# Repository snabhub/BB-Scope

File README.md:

# Bread Board Scope (Mini Oscilloscope + Function Generator)
- This is the repositiory of Group 36 ELEC3300 Fall 2022.

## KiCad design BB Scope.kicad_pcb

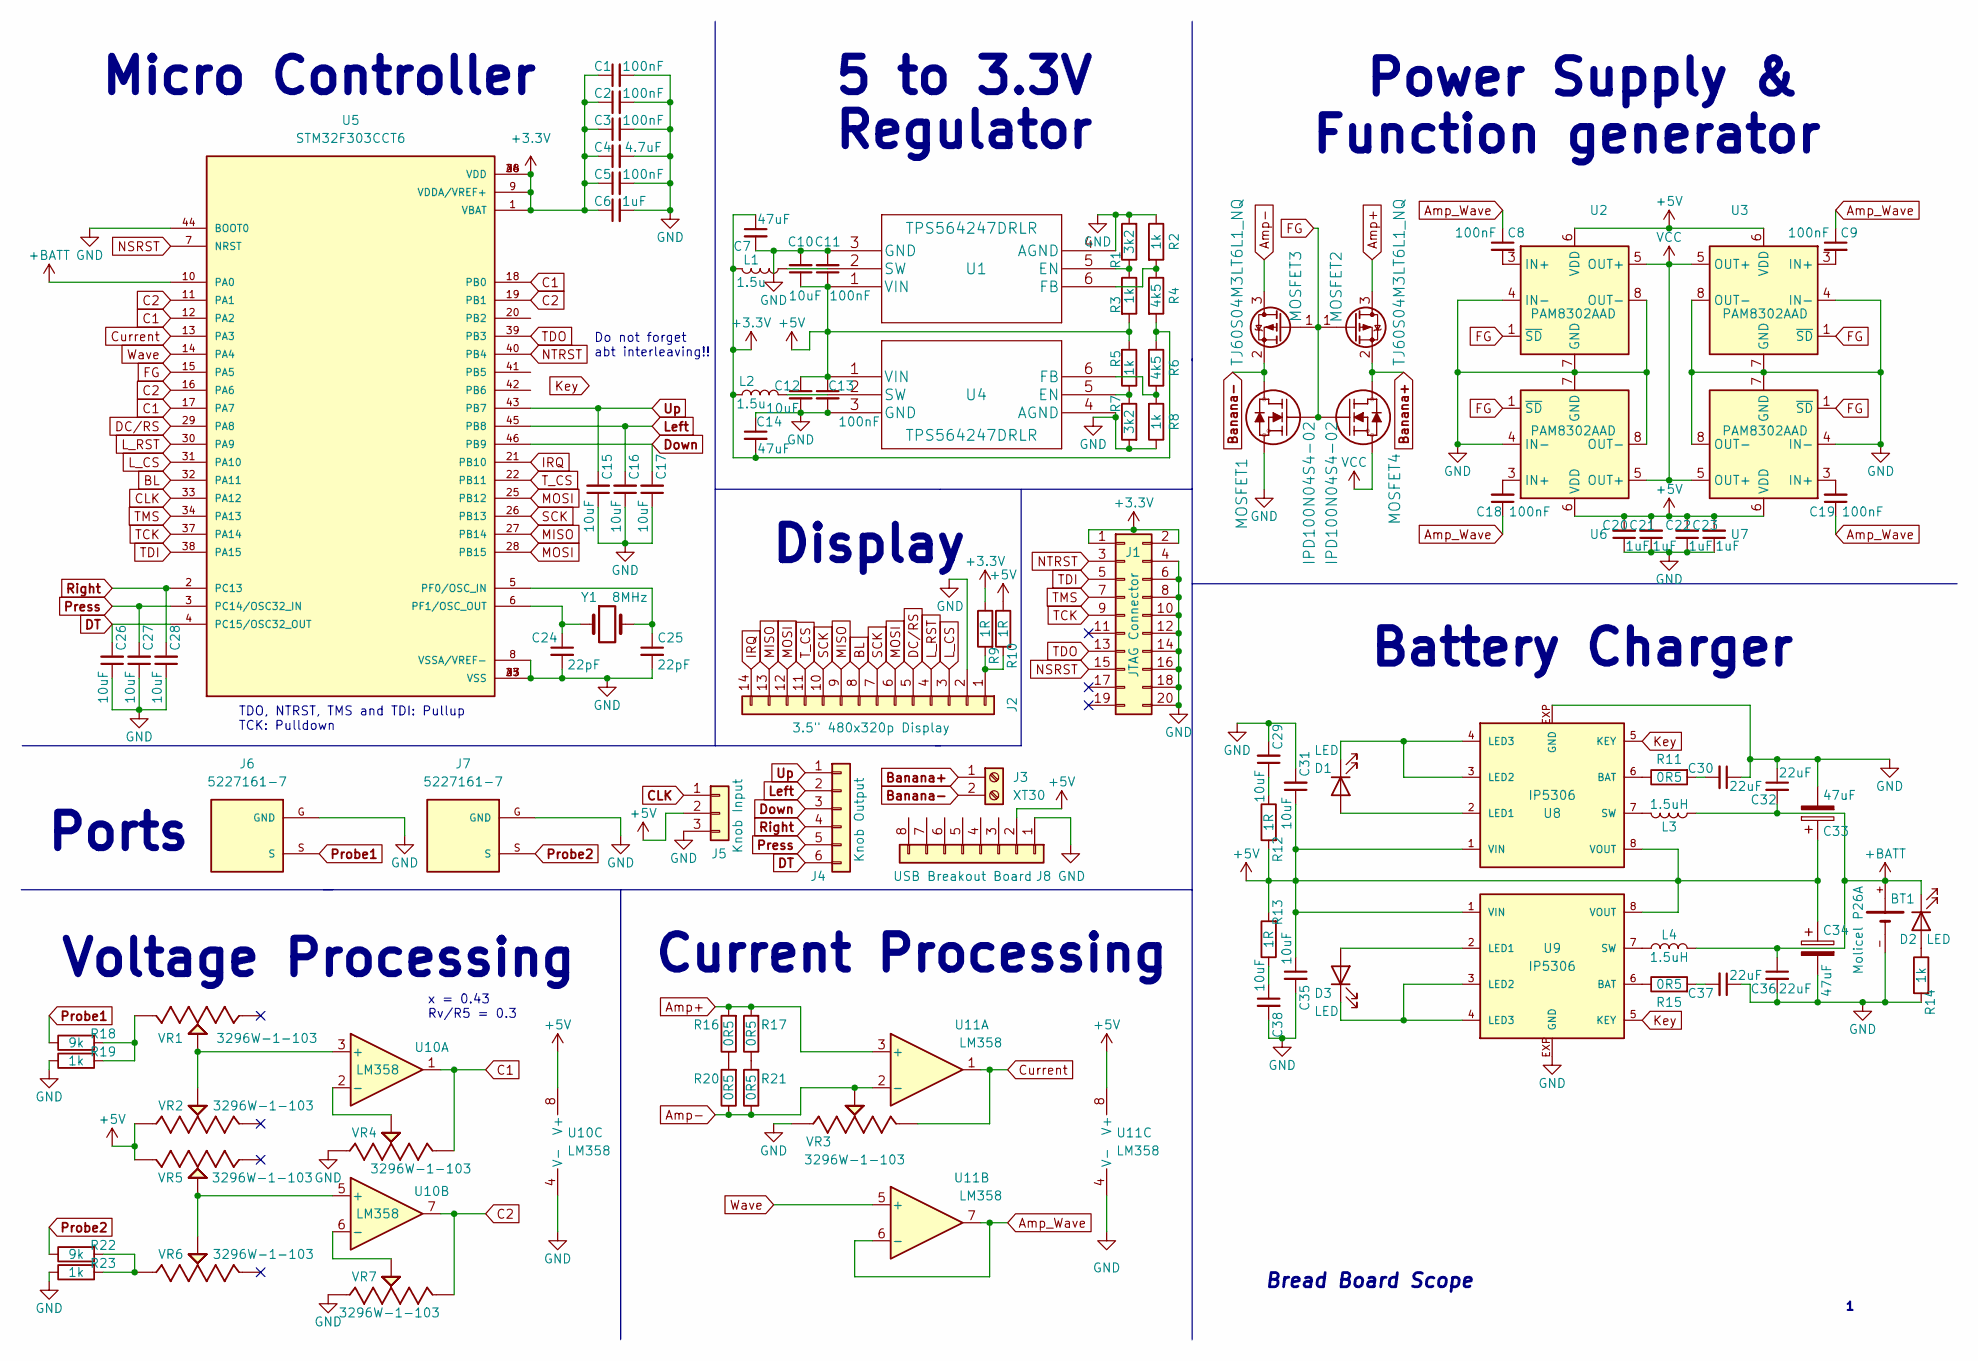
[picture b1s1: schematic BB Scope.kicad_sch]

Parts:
BT1: Molicel P26A; 18650 Case
C1, C2, C3, C5, C8, C9, C11, C13, C18, C19: 100nF; C_0805_2012Metric_Pad1.18x1.45mm_HandSolder
C4: 4.7uF; C_0805_2012Metric_Pad1.18x1.45mm_HandSolder
C6, C20, C21, C22, C23: 1uF; C_0805_2012Metric_Pad1.18x1.45mm_HandSolder
C7, C14: 47uF; C_0805_2012Metric_Pad1.18x1.45mm_HandSolder
C10, C12, C15, C16, C17, C26, C27, C28, C29, C31, C35, C38: 10uF; C_0805_2012Metric_Pad1.18x1.45mm_HandSolder
C24, C25: 22pF; C_0805_2012Metric_Pad1.18x1.45mm_HandSolder
C30, C32, C36, C37: 22uF; C_0805_2012Metric_Pad1.18x1.45mm_HandSolder
C33, C34: 47uF; CP_Elec_5x3
D1, D3: LED; LED_0805_2012Metric
D2: LED; PinHeader_1x02_P2.54mm_Vertical
J1: JTAG Connector; PinHeader_2x10_P2.54mm_Vertical
J2: 3.5" 480x320p Display; PinHeader_1x14_P2.54mm_Vertical
J3: XT30; AMASS_XT30U-F_1x02_P5.0mm_Vertical
J4: Knob Output; PinHeader_1x06_P2.54mm_Vertical
J5: Knob Input; PinHeader_1x03_P2.54mm_Vertical
J6, J7: 5227161-7; TE_5227161-7
J8: USB Breakout Board; PinHeader_1x08_P2.54mm_Vertical
L1, L2: 1.5u; L_Coilcraft_LPS4018
L3, L4: 1.5uH; L_Coilcraft_LPS4018
MOSFET1, MOSFET2: TJ60S04M3LT6L1_NQ; TJ60S04M3L
MOSFET3, MOSFET4: IPD100N04S4-02; IPD100N04S402
R1, R7: 3k2; R_0805_2012Metric_Pad1.20x1.40mm_HandSolder
R2, R3, R5, R8, R14, R19, R23: 1k; R_0805_2012Metric_Pad1.20x1.40mm_HandSolder
R4, R6: 4k5; R_0805_2012Metric_Pad1.20x1.40mm_HandSolder
R9, R10, R12, R13: 1R; R_0805_2012Metric_Pad1.20x1.40mm_HandSolder
R11, R15, R16, R17, R20, R21: 0R5; RESC6331X70N
R18, R22: 9k; R_0805_2012Metric_Pad1.20x1.40mm_HandSolder
U1, U4: TPS564247DRLR; TPS-564247DRLR
U2, U3, U6, U7: PAM8302AAD; SOIC-8-1EP_3.9x4.9mm_P1.27mm_EP2.41x3.3mm
U5: STM32F303CCT6; QFP50P900X900X160-48N; PARTREV 14
U8, U9: IP5306; SOIC127P599X175-9N
U10, U11: LM358; SOIC-8-1EP_3.9x4.9mm_P1.27mm_EP2.29x3mm
VR1, VR2, VR3, VR4, VR5, VR6, VR7: 3296W-1-103; TRIM_3296W-1-101; PARTREV 05/16
Y1: 8MHz; Crystal_SMD_SeikoEpson_MA505-2Pin_12.7x5.1mm_HandSoldering

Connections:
+3.3V: C1.1, C2.1, C3.1, C4.1, C5.1, C6.1, C7.1, C14.2, J1.1, J1.2, L1.1, L2.1, R4.2, R6.2, R9.1, U5.1 (VBAT), U5.9 (VDDA/VREF+), U5.24 (VDD), U5.36 (VDD), U5.48 (VDD)
+5V: C10.1, C11.1, C12.1, C13.1, C20.2, C21.2, C22.2, C23.2, C31.1, C33.1, C34.1, C35.1, J5.2, J8.2, R3.2, R5.2, R10.1, R12.2, R13.2, U1.1 (VIN), U2.6 (VDD), U3.6 (VDD), U4.1 (VIN), U6.6 (VDD), U7.6 (VDD), U8.1 (VIN), U8.8 (VOUT), U9.1 (VIN), U9.8 (VOUT), U10.8 (V+), U11.8 (V+), VR2.1, VR5.3
+BATT: BT1.+, C32.2, C36.1, D2.1 (K), L3.2, L4.2, U5.10 (PA0)
Amp+: MOSFET2.3 (D), R16.2, R17.2, U11.3 (+)
Amp-: MOSFET1.3 (D), R20.1, R21.1, U11.2 (-), VR3.2
Amp_Wave: C8.1, C9.1, C18.1, C19.1, U11.6 (-), U11.7
BL: J2.8, U5.32 (PA11)
Banana+: J3.1, MOSFET2.2 (S), MOSFET4.2
Banana-: J3.2, MOSFET1.2 (S), MOSFET3.2
C1: U5.12 (PA2), U5.17 (PA7), U5.18 (PB0), U10.1, VR4.3
C2: U5.11 (PA1), U5.16 (PA6), U5.19 (PB1), U10.7, VR7.3
CLK: J5.1, U5.33 (PA12)
Current: U5.13 (PA3), U11.1, VR3.3
DC/RS: J2.5, U5.29 (PA8)
DT: C26.2, J4.6, U5.4 (PC15/OSC32_OUT)
Down: C17.2, J4.3, U5.46 (PB9)
FG: MOSFET1.1 (G), MOSFET2.1 (G), MOSFET3.1, MOSFET4.1, U2.1 (~SD), U3.1 (~SD), U5.15 (PA5), U6.1 (~SD), U7.1 (~SD)
GND: BT1.-, C1.2, C2.2, C3.2, C4.2, C5.2, C6.2, C7.2, C10.2, C11.2, C12.2, C13.2, C14.1, C15.1, C16.1, C17.1, C20.1, C21.1, C22.1, C23.1, C24.2, C25.2, C26.1, C27.1, C28.1, C29.2, C30.1, C31.2, C32.1, C33.2, C34.2, C35.2, C36.2, C37.1, C38.2, J1.4, J1.6, J1.8, J1.10, J1.12, J1.14, J1.16, J1.18, J1.20, J2.2, J5.3, J6.G (GND), J7.G (GND), J8.1, MOSFET3.3, R1.2, R2.1, R7.2, R8.1, R14.2, R19.1, R23.1, U1.3 (GND), U1.4 (AGND), U2.4 (IN-), U2.7 (GND), U2.8 (OUT-), U2.9, U3.4 (IN-), U3.7 (GND), U3.8 (OUT-), U3.9, U4.3 (GND), U4.4 (AGND), U5.8 (VSSA/VREF-), U5.23 (VSS), U5.35 (VSS), U5.44 (BOOT0), U5.47 (VSS), U6.4 (IN-), U6.7 (GND), U6.8 (OUT-), U6.9, U7.4 (IN-), U7.7 (GND), U7.8 (OUT-), U7.9, U8.9, U8.EXP (GND), U9.9, U9.EXP (GND), U10.4 (V-), U10.9, U11.4 (V-), VR3.1, VR4.1, VR7.1
IRQ: J2.14, U5.21 (PB10)
Key: U8.5 (KEY), U9.5 (KEY)
L_CS: J2.3, U5.31 (PA10)
L_RST: J2.4, U5.30 (PA9)
Left: C16.2, J4.2, U5.45 (PB8)
MISO: J2.9, J2.13, U5.27 (PB14)
MOSI: J2.6, J2.12, U5.25 (PB12), U5.28 (PB15)
NSRST: J1.15, U5.7 (NRST)
NTRST: J1.3, U5.40 (PB4)
unnamed: C8.2, U2.3 (IN+)
unnamed: C9.2, U3.3 (IN+)
unnamed: C18.2, U6.3 (IN+)
unnamed: C19.2, U7.3 (IN+)
unnamed: C24.1, U5.6 (PF1/OSC_OUT), Y1.1
unnamed: C25.1, U5.5 (PF0/OSC_IN), Y1.2
unnamed: C29.1, R12.1
unnamed: C30.2, R11.2
unnamed: C37.2, R15.2
unnamed: C38.1, R13.1
unnamed: D1.1 (K), U8.3 (LED2), U8.4 (LED3)
unnamed: D1.2 (A), U8.2 (LED1)
unnamed: D2.2 (A), R14.1
unnamed: D3.1 (K), U9.3 (LED2), U9.4 (LED3)
unnamed: D3.2 (A), U9.2 (LED1)
unnamed: J2.1, R9.2, R10.2
unnamed: L1.2, U1.2 (SW)
unnamed: L2.2, U4.2 (SW)
unnamed: L3.1, U8.7 (SW)
unnamed: L4.1, U9.7 (SW)
unnamed: R1.1, R3.1, U1.5 (EN)
unnamed: R2.2, R4.1, U1.6 (FB)
unnamed: R5.1, R7.1, U4.5 (EN)
unnamed: R6.1, R8.2, U4.6 (FB)
unnamed: R11.1, U8.6 (BAT)
unnamed: R15.1, U9.6 (BAT)
unnamed: R16.1, R20.2
unnamed: R17.1, R21.2
unnamed: R18.2, R19.2, VR1.3
unnamed: R22.2, R23.2, VR6.1
unnamed: U10.2 (-), VR4.2
unnamed: U10.3 (+), VR1.2, VR2.2
unnamed: U10.5 (+), VR5.2, VR6.2
unnamed: U10.6 (-), VR7.2
Press: C27.2, J4.5, U5.3 (PC14/OSC32_IN)
Probe1: J6.S, R18.1
Probe2: J7.S, R22.1
Right: C28.2, J4.4, U5.2 (PC13)
SCK: J2.7, J2.10, U5.26 (PB13)
TCK: J1.9, U5.37 (PA14)
TDI: J1.5, U5.38 (PA15)
TDO: J1.13, U5.39 (PB3)
TMS: J1.7, U5.34 (PA13)
T_CS: J2.11, U5.22 (PB11)
Up: C15.2, J4.1, U5.43 (PB7)
VCC: MOSFET4.3, U2.5 (OUT+), U3.5 (OUT+), U6.5 (OUT+), U7.5 (OUT+)
Wave: U5.14 (PA4), U11.5 (+)

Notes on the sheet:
Current Processing
5 to 3.3V
Bread Board Scope
Micro Controller
Voltage Processing
Do not forget abt interleaving!!
Regulator
Display
x = 0.43 Rv/R5 = 0.3
Ports
Battery Charger
Power Supply & Function generator
TDO, NTRST, TMS and TDI: Pullup TCK: Pulldown

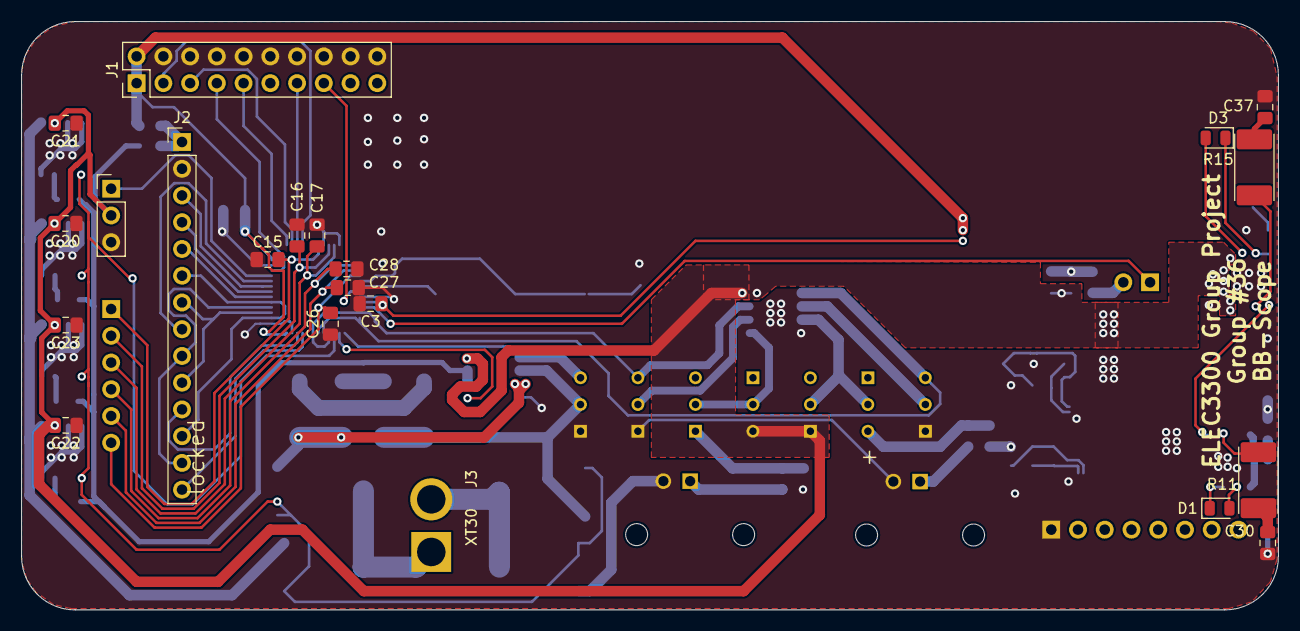
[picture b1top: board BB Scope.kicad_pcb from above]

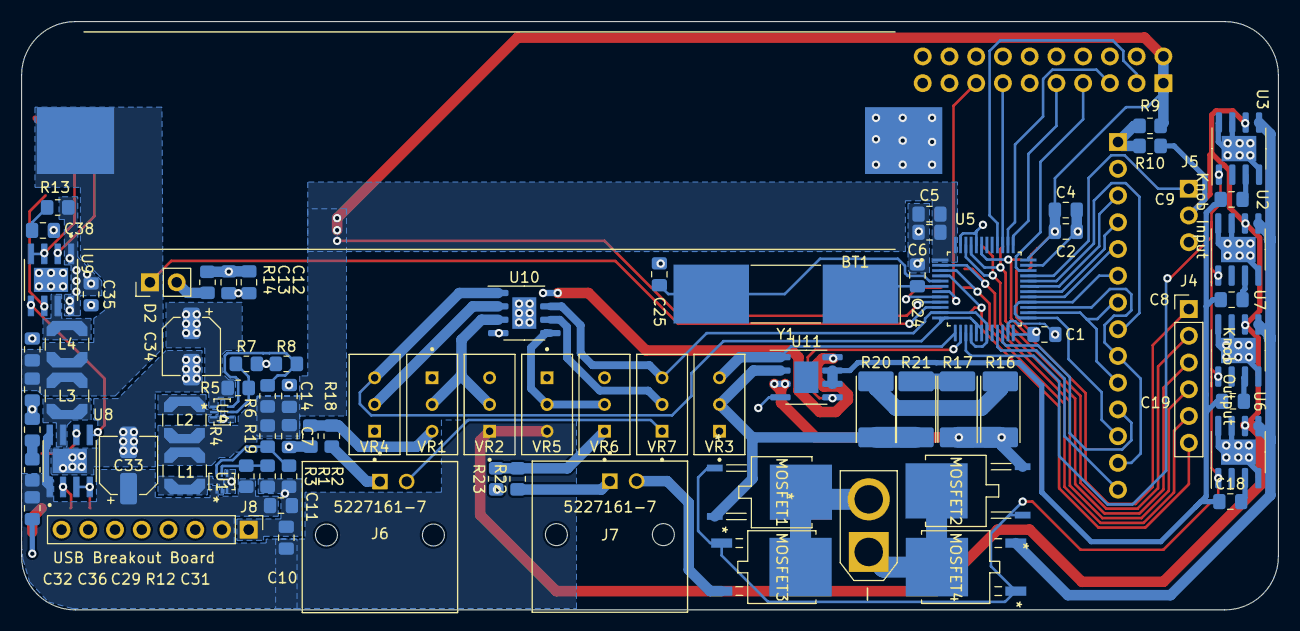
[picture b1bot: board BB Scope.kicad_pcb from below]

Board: 2 copper layers, 119.4 x 55.9 mm, 100 parts (80 on the bottom side), 74 nets.

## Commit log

2022-11-06 5- function implementation
2022-11-15 Workable
2022-11-15 Need to enable continuous mode
2022-11-17 Backup
2022-11-17 William's code
2022-11-17 Dynamic Horizonal Position and Scale
2022-11-17 Try Horizon Scale
2022-11-23 Time Scale and Freeze
2022-11-23 Tolerate maximum about 50k Hz
2022-12-03 Final
2022-12-03 Self-made Fonts

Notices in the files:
parts and their libraries:
Copyright 2021 Accelerated Designs. All rights reserved.
